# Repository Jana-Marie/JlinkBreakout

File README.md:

# JlinkBreakout

Segger Jlink to Tag-Connect/SWD breakout board.

## [V2](V2/)
Notes:
 - Use a right-angle 2 row, 20 position 0.1" (2.54mm) female header/socket
     + https://lcsc.com/product-detail/Pin-Header-Female-Header_Ckmtw-Shenzhen-Cankemeng-C124406_C124406.html

## [V3](V3/)
- Adds a voltage regulator with selectable output voltage (3.3V, 2.5V, 1.8V, External power)
- JST-XH connector for SWD
- 2x3 IDC Tag-connect header
- JTAG connector is standard 2 row, 20 position 0.1" (2.54mm) female header/socker, mounted on pcb edge
    + https://lcsc.com/product-detail/Pin-Header-Female-Header_BOOMELE-Boom-Precision-Elec-C30867_C30867.html
        * Pin thickness: 0.32mm to .064mm
        * Pin-pin clearance: 2.22mm to 1.9mm
    + Standard 1.6mm (0.062") PCB should be solderable, but there will be a gap, or 2mm (0.079") PCB would leave less clearance

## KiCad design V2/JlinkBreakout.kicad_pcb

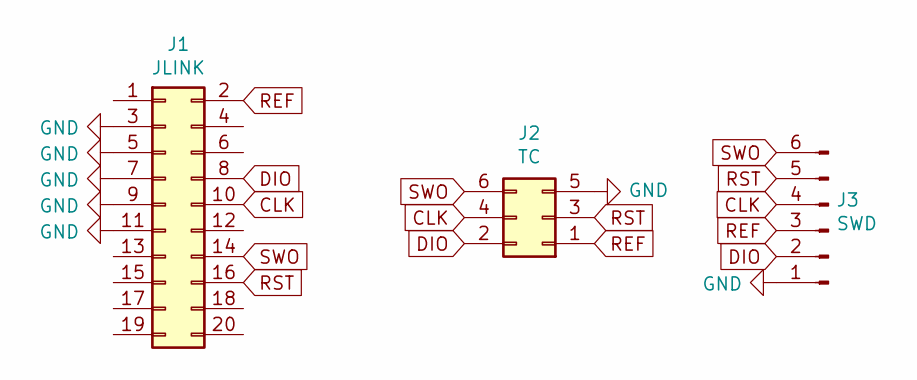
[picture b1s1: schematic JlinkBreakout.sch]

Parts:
J1: JLINK; PinHeader_2x10_P2.54mm_Vertical
J2: TC; PinHeader_2x03_P2.54mm_Vertical
J3: SWD; PinHeader_1x06_P2.54mm_Vertical

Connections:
CLK: J1.10, J2.4, J3.4
DIO: J1.8, J2.2, J3.2
GND: J1.3, J1.5, J1.7, J1.9, J1.11, J2.5, J3.1
REF: J1.2, J2.1, J3.3
RST: J1.16, J2.3, J3.5
SWO: J1.14, J2.6, J3.6

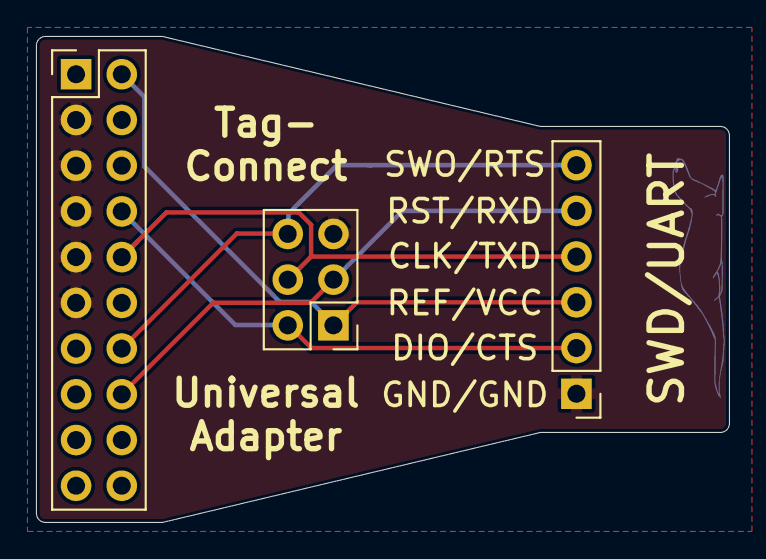
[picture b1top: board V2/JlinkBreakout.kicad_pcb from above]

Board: 2 copper layers, 38.5 x 27.0 mm, 3 parts (0 on the bottom side), 6 nets.

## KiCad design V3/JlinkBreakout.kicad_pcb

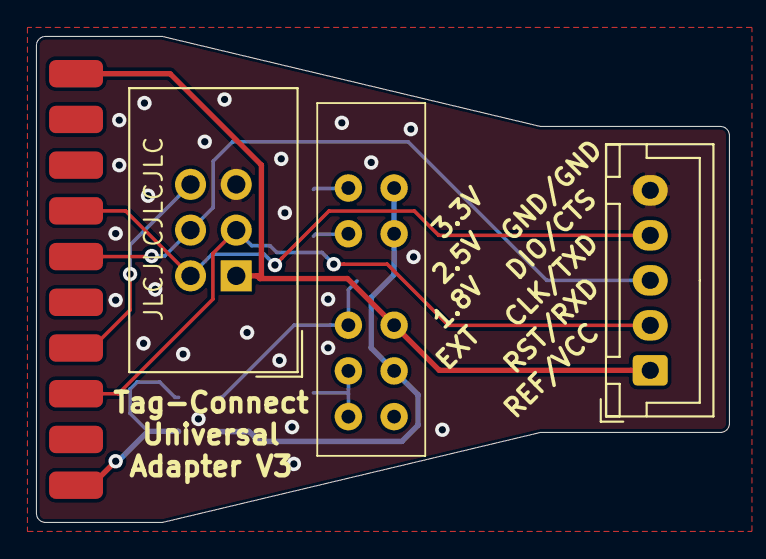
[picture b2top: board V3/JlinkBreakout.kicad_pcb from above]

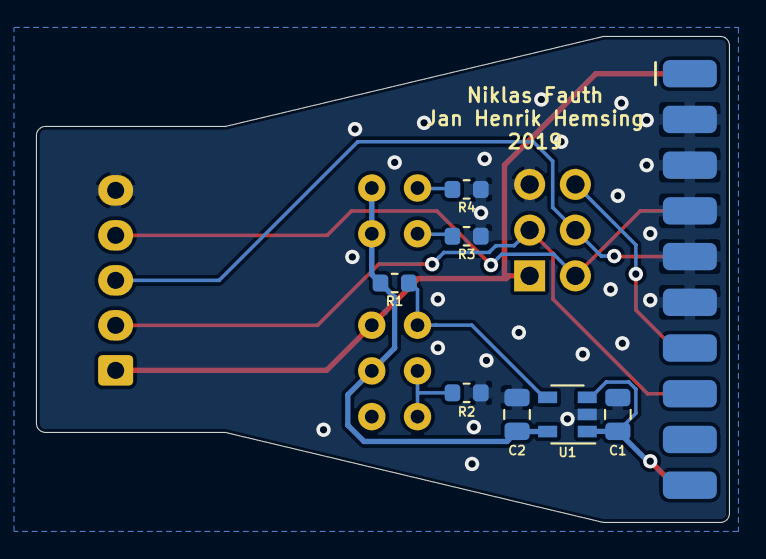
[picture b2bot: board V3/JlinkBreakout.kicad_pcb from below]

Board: 2 copper layers, 38.5 x 27.0 mm, 11 parts (7 on the bottom side), 12 nets.

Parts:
C1, C2: 1u; C_0805_2012Metric
J1: JLINK; conn_02x10_edge
J2: TC; IDC-Header_2x03_P2.54mm_Vertical
J3: SWD; JST_XH_B5B-XH-A_1x05_P2.50mm_Vertical
R1: 10k; R_0603_1608Metric
R2: 17.5k; R_0603_1608Metric
R3: 10.8k; R_0603_1608Metric
R4: 5k; R_0603_1608Metric
U1: SGM2019; SOT-23-5
U2: switch_0204; SS-24E06-TG

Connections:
+5V: C1.1, J1.20, U1.1, U1.3
CLK: J1.10, J2.4, J3.3
DIO: J1.8, J2.2, J3.4
GND: C1.2, C2.2, J1.3, J1.5, J1.7, J1.9, J1.11, J2.5, J3.5, R2.1, R3.1, R4.1, U1.2
LDOOUT: C2.1, R1.1, U1.5, U2.2, U2.4, U2.5
unnamed: R1.2, U1.4, U2.8
unnamed: R2.2, U2.6, U2.7
unnamed: R3.2, U2.9
unnamed: R4.2, U2.10
REF: J1.2, J2.1, J3.1, U2.3
RST: J1.16, J2.3, J3.2
SWO: J1.14, J2.6

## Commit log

2019-05-06 added gitignore
2019-05-06 initital commit
2019-05-06 added image to readme
2019-05-06 updated gitignore
2019-05-06 removed fp-info-cache
2019-05-06 added gerber
2019-11-01 created V2
2019-11-01 remove old files
2019-11-02 finalized V2
2019-11-02 removed old files
2019-11-02 added image
2019-11-02 moved V2 to V3
2019-11-02 moved V1 to V2
2019-11-02 removed V2
2019-11-02 added V2
2019-11-02 removed V1
2019-11-02 updated gerber
2019-11-26 updated Resistor values
2019-12-02 fixed footprint
2020-07-22 Add V3 BOM
2020-07-22 Add notes in README
